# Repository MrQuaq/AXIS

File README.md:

# **AXIS — Balancing robot**

***AXIS is a dual wheeled self-balancing robot built around an ESP32 and custom PCB!***

### **Project overview**

AXIS is a dual wheeled balancing robot, using a PID algorithm to keep its balance. The main microcontroller of the robot will be the ESP32. This enables the use of an Xbox controller for controlling the robot. Certain buttons on the controller will be mapped to the pid value settings so they can be changed on the fly, which should make the tuning process a lot easier.

As an additional feature that will be tested after the robot is already stable, 2 encoders that are already mounted on the motors will be added. Their data will be used in a second PID algorithm to hopefully get the robot to stay in a single place a lot easier. This feature is still completely optional and can easily be turned on by a button on the Xbox controller.

### **Goals**

The goal of this project is to become more familiarized with electronics to get a good foundation for future projects. And to grasp the basics of PCB-design.

The goal for the robot itself is to make it balance without jittering too much and to make it drivable via a controller.

### **Key components**

- Custom PCB to mount breakout boards on  
- 3D-printed frame  
- Custom code featuring a PID algorithm and bluetooth connection

### **PCB design**

This PCB features lots of female header pins to mount existing breakout boards onto. This framework makes for more reliable connections and pcb-design experience.  
To design the board I used KiCAD, a free open-source EDA.

The first step in the design process was coming up with the requirements and features of the board.  
These include:

- Measuring the robots angle reliably  
- Driving the motors  
- Being able to connect a small lcd display for easier status updates and eventually PID tuning  
- Accept power from a 7,2V NiMH battery  
- Have connectors for encoders

After setting these requirements, a schematic was designed before moving on to the actual tracing. This also enabled me to become even more familiarized with the design and the components.

With the schematic made, the pcb tracing was fairly easy. I paid special attention to the spacing between the female pin headers so the modules would fit properly. A ground plane was also added on the bottom of the PCB to make wiring easier. To disturb this plane as little as possible, I tried to lay out the PCB in such a way that I have almost no traces on the back side.  
The final PCB features:

- Headers for ESP32  
- Headers for IMU module (ICM20948)  
- Headers for motor driver (tb6612fng)  
- Headers for lcd display  
- Screw terminals for motors and encoders  
- Components to provide the right (and stable) voltages to all components  
- Protection components

### **3D-CAD**

For the CAD I used a program I’m fairly familiar with; Fusion 360.  
The frame is divided into 3 key parts:

- Motor mount  
- Bottom compartment  
- Top compartment

The motor mount is made so that the motor has no room to shake. This results in a weird internal shape because of the irregular shape of the motor with right angle gearbox. Additionally the motor is able to be secured with 4 screws via the motor mount cover. This cover also features some cooling slots (but I doubt I need them).

Further up, we have the bottom compartment of the head. This houses the custom PCB. Connections to the encoders and motors pass through the bottom to the motor mount.

Above, there is the top compartment of the head. Here is the battery, LCD screen and switch. Again, their connections will pass through the bottom to the compartment below.  
Finally a lid, secured with magnets for easy access, covers up the top.

### **Timeline**

What’s already been done:

- Full code (imu, controller, PID’s and motor)  
- PCB design in KiCad  
- IMU testing  
- Motor testing  
- PID testing (imu and motor)  
- 3D-CAD

What still needs to be done:

- 3D printing the frame  
- Ordering the PCB  
- Final assembly  
- PID tuning

### **Gallery**

##### 3D-CAD

| | |
| :---: | :---: |
|  |  |
|  |  |
|  |  |
|  |  |

##### PCB-design

| | |
| :---: | :---: |
|  |  |
|  | |

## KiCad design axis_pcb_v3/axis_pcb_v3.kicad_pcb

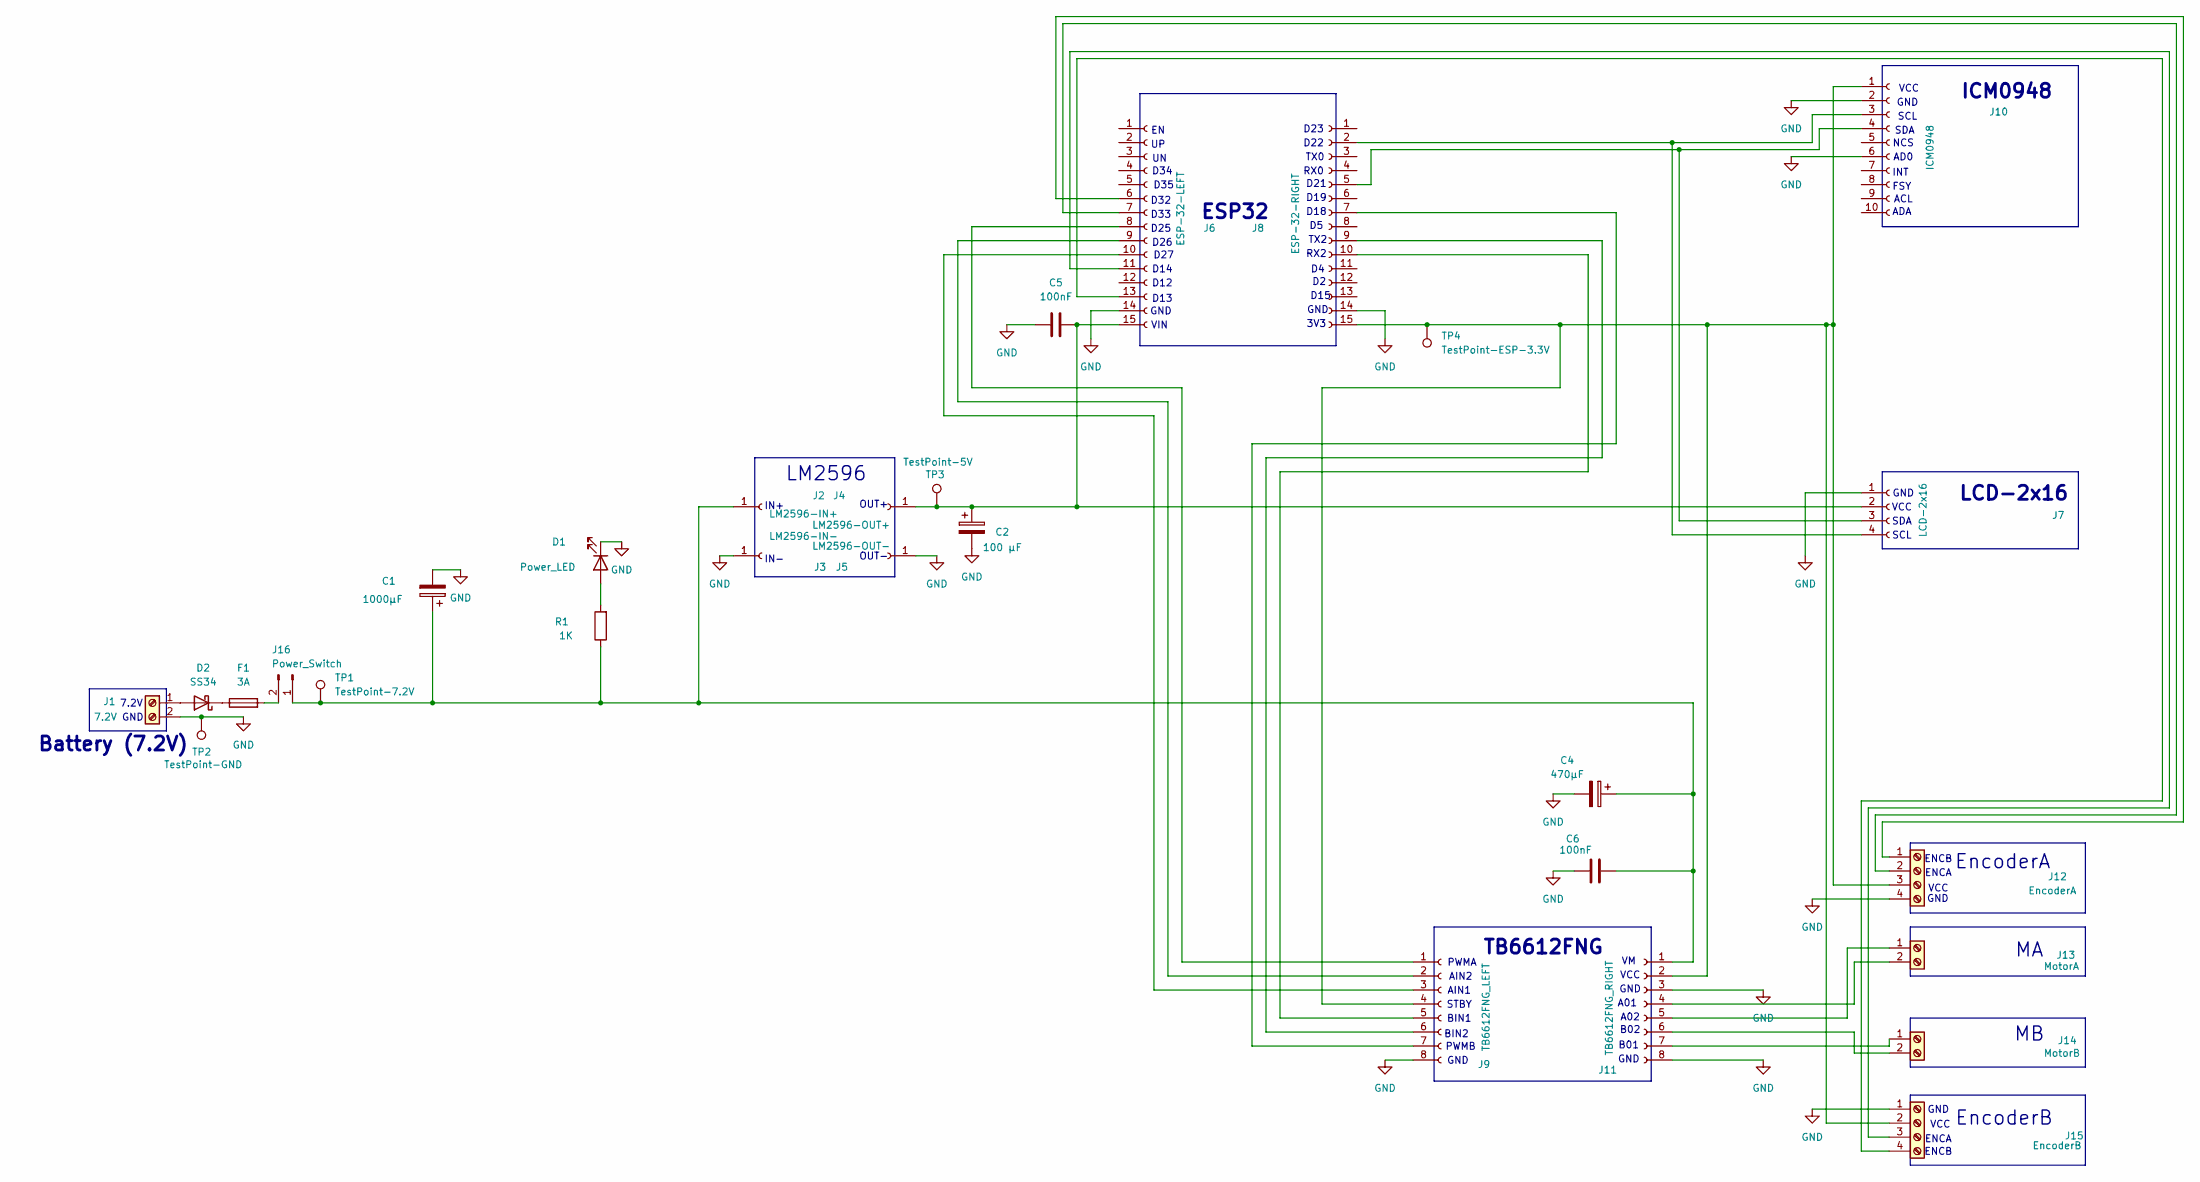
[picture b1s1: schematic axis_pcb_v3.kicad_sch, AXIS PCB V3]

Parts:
C1: 1000µF; CP_Radial_D10.0mm_P5.00mm
C2: 100 µF; CP_Radial_D8.0mm_P3.50mm
C4: 470µF; CP_Radial_D8.0mm_P3.50mm
C5, C6: 100nF; C_0805_2012Metric
D1: Power_LED; LED_0805_2012Metric
D2: SS34; D_SMA
F1: 3A; Fuseholder_Blade_Mini_Keystone_3568
J1: 7.2V; TerminalBlock_Phoenix_MKDS-1,5-2_1x02_P5.00mm_Horizontal
J2: LM2596-IN+; PinSocket_1x01_P2.54mm_Vertical
J3: LM2596-IN-; PinSocket_1x01_P2.54mm_Vertical
J4: LM2596-OUT+; PinSocket_1x01_P2.54mm_Vertical
J5: LM2596-OUT-; PinSocket_1x01_P2.54mm_Vertical
J6: ESP-32-LEFT; PinSocket_1x15_P2.54mm_Vertical
J7: LCD-2x16; PinSocket_1x04_P2.54mm_Vertical
J8: ESP-32-RIGHT; PinSocket_1x15_P2.54mm_Vertical
J9: TB6612FNG_LEFT; PinSocket_1x08_P2.54mm_Vertical
J10: ICM0948; PinSocket_1x10_P2.54mm_Vertical
J11: TB6612FNG_RIGHT; PinSocket_1x08_P2.54mm_Vertical
J12: EncoderA; TerminalBlock_Phoenix_MKDS-1,5-4_1x04_P5.00mm_Horizontal
J13: MotorA; TerminalBlock_Phoenix_MKDS-1,5-2_1x02_P5.00mm_Horizontal
J14: MotorB; TerminalBlock_Phoenix_MKDS-1,5-2_1x02_P5.00mm_Horizontal
J15: EncoderB; TerminalBlock_Phoenix_MKDS-1,5-4_1x04_P5.00mm_Horizontal
J16: Power_Switch; JST_XH_B2B-XH-A_1x02_P2.50mm_Vertical
R1: 1K; R_0805_2012Metric
TP1: TestPoint-7.2V; TestPoint_Pad_D1.5mm
TP2: TestPoint-GND; TestPoint_Pad_D1.5mm
TP3: TestPoint-5V; TestPoint_Pad_D1.5mm
TP4: TestPoint-ESP-3.3V; TestPoint_Pad_D1.5mm

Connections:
GND: C1.2, C2.2, C4.2, C5.1, C6.1, D1.1 (K), J1.2, J3.1, J5.1, J6.14, J7.1, J8.14, J9.8, J10.2, J10.6, J11.3, J11.8, J12.4, J15.1, TP2.1
unnamed: D1.2 (A), R1.2
unnamed: D2.2 (A), J1.1
unnamed: D2.1 (K), F1.1
unnamed: C2.1, C5.2, J4.1, J6.15, J7.2, TP3.1
unnamed: J6.8, J9.1
unnamed: J6.9, J9.2
unnamed: J6.10, J9.3
unnamed: J8.7, J9.7
unnamed: J8.9, J9.6
unnamed: J8.10, J9.5
unnamed: J8.15, J9.4, J10.1, J11.2, J12.3, J15.2, TP4.1
unnamed: J7.4, J8.2, J10.3
unnamed: J7.3, J8.5, J10.4
unnamed: C1.1, C4.1, C6.2, J2.1, J11.1, J16.1, R1.1, TP1.1
unnamed: J11.4, J13.2
unnamed: J11.5, J13.1
unnamed: J11.6, J14.2
unnamed: J11.7, J14.1
unnamed: J6.6, J12.1
unnamed: J6.7, J12.2
unnamed: J6.11, J15.3
unnamed: J6.13, J15.4
unnamed: F1.2, J16.2

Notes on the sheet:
EncoderB
PWMA
3V3
D35
D25
D12
ENCA
BIN1
ACL
D26
LM2596
VCC
D34
D13
D21
INT
SCL
VIN
GND
SDA
AIN1
RX0
OUT+
D23
TX0
A02
7.2V
TB6612FNG
B01
D19
TX2
AD0
STBY
OUT-
D22
NCS
EncoderA
ENCB
RX2
ADA

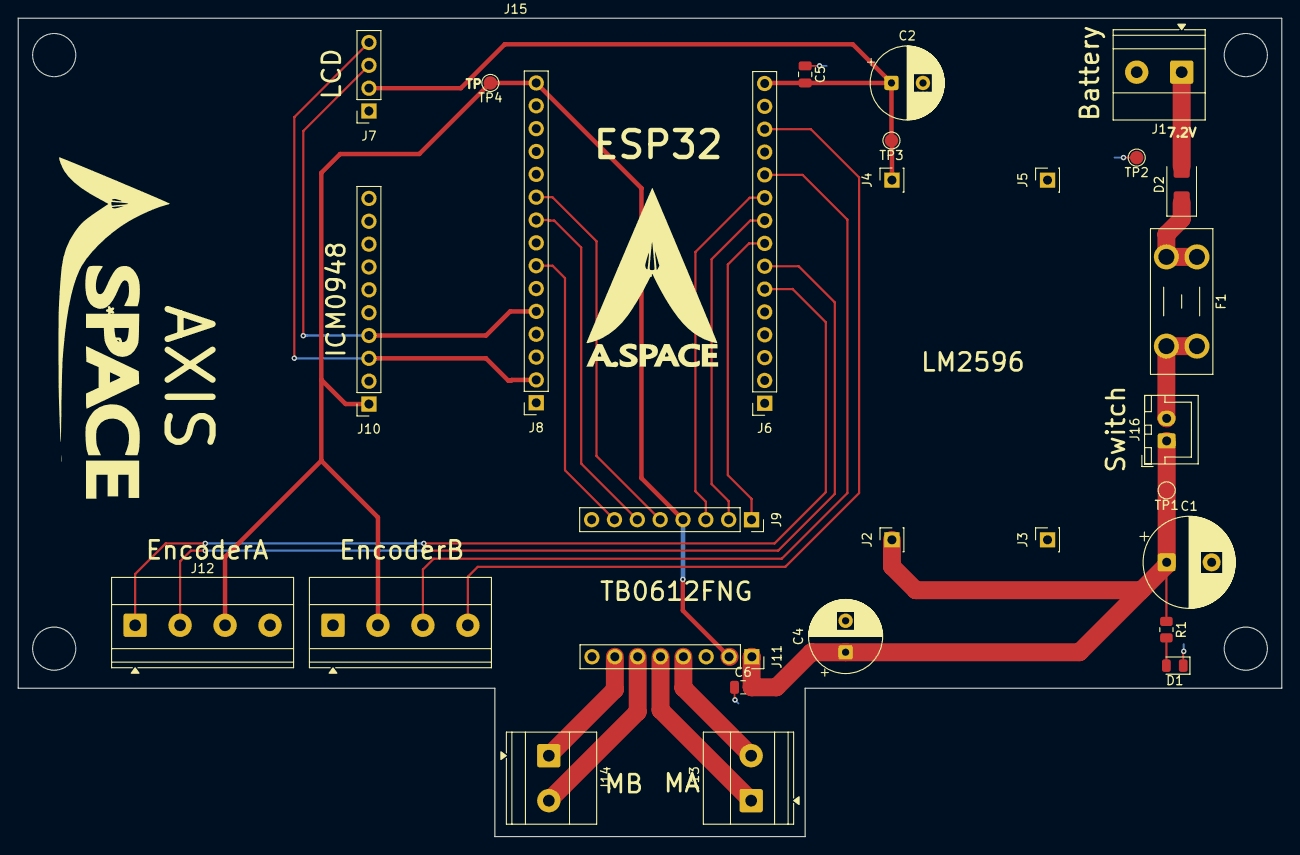
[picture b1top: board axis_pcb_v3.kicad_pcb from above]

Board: 2 copper layers, 140.5 x 91.0 mm, 29 parts (0 on the bottom side), 24 nets.

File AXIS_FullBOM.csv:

Id,Designator,Footprint,Quantity,Designation,Supplier and ref,In possesion
1,D1,LED_0805_2012Metric,1,Power_LED,,FALSE
2,J4,PinSocket_1x01_P2.54mm_Vertical,1,LM2596-OUT+,,FALSE
3,"C5,C6",C_0805_2012Metric,2,100nF,,FALSE
4,TP2,TestPoint_Pad_D1.5mm,1,TestPoint-GND,,FALSE
5,J6,PinSocket_1x15_P2.54mm_Vertical,1,ESP-32-LEFT,,FALSE
6,J14,"TerminalBlock_Phoenix_MKDS-1,5-2_1x02_P5.00mm_Horizontal",1,MotorB,,FALSE
7,TP4,TestPoint_Pad_D1.5mm,1,TestPoint-ESP-3.3V,,FALSE
8,J13,"TerminalBlock_Phoenix_MKDS-1,5-2_1x02_P5.00mm_Horizontal",1,MotorA,,FALSE
9,J15,"TerminalBlock_Phoenix_MKDS-1,5-4_1x04_P5.00mm_Horizontal",1,EncoderB,,FALSE
10,TP1,TestPoint_Pad_D1.5mm,1,TestPoint-7.2V,,FALSE
11,C1,CP_Radial_D10.0mm_P5.00mm,1,1000µF,,FALSE
12,J1,"TerminalBlock_Phoenix_MKDS-1,5-2_1x02_P5.00mm_Horizontal",1,7.2V,,FALSE
13,D2,D_SMA,1,SS34,,FALSE
14,J10,PinSocket_1x10_P2.54mm_Vertical,1,ICM0948,,FALSE
15,C4,CP_Radial_D8.0mm_P3.50mm,1,470µF,,FALSE
16,J9,PinSocket_1x08_P2.54mm_Vertical,1,TB6612FNG_LEFT,,FALSE
17,J3,PinSocket_1x01_P2.54mm_Vertical,1,LM2596-IN-,,FALSE
18,J8,PinSocket_1x15_P2.54mm_Vertical,1,ESP-32-RIGHT,,FALSE
19,J11,PinSocket_1x08_P2.54mm_Vertical,1,TB6612FNG_RIGHT,,FALSE
20,J7,PinSocket_1x04_P2.54mm_Vertical,1,LCD-2x16,,FALSE
21,J5,PinSocket_1x01_P2.54mm_Vertical,1,LM2596-OUT-,,FALSE
22,J16,JST_XH_B2B-XH-A_1x02_P2.50mm_Vertical,1,Power_Switch,,FALSE
23,F1,Fuseholder_Blade_Mini_Keystone_3568,1,3A,,FALSE
24,J2,PinSocket_1x01_P2.54mm_Vertical,1,LM2596-IN+,,FALSE
25,C2,CP_Radial_D8.0mm_P3.50mm,1,100 µF,,FALSE
26,TP3,TestPoint_Pad_D1.5mm,1,TestPoint-5V,,FALSE
27,R1,R_0805_2012Metric,1,1K,,FALSE
28,J12,"TerminalBlock_Phoenix_MKDS-1,5-4_1x04_P5.00mm_Horizontal",1,EncoderA,,FALSE
,,,,,,
Part,Quantity,In possesion,,,,
 ESP-32 module,1,TRUE,,,,
TB6612FNG module,1,TRUE,,,,
LM2596 module,1,TRUE,,,,
DC motor with encoder,2,TRUE,,,,
16 char LCD display,1,TRUE,,,,
"7,2V Ni Mah battery",1,TRUE,,,,
switch,1,TRUE,,,,
,,,,,,
Part,Quantity,In possesion,,,,
1kg PLA filament,1,FALSE,,,,
Wheel,2,TRUE,,,,

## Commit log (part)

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2026-06-04 Add project title and description to README
2026-06-04 moving files from drive to github
2026-06-17 Enhance README with detailed project description
    Expanded project description to include details about control, sensors, and components.
2026-06-17 Update README to include PCB section and image
    Added a section about the PCB with an image.
2026-06-22 updated code for new imu
2026-06-24 Revise README with project details and goals
    Expanded project description and goals, added details on PCB design and components.
